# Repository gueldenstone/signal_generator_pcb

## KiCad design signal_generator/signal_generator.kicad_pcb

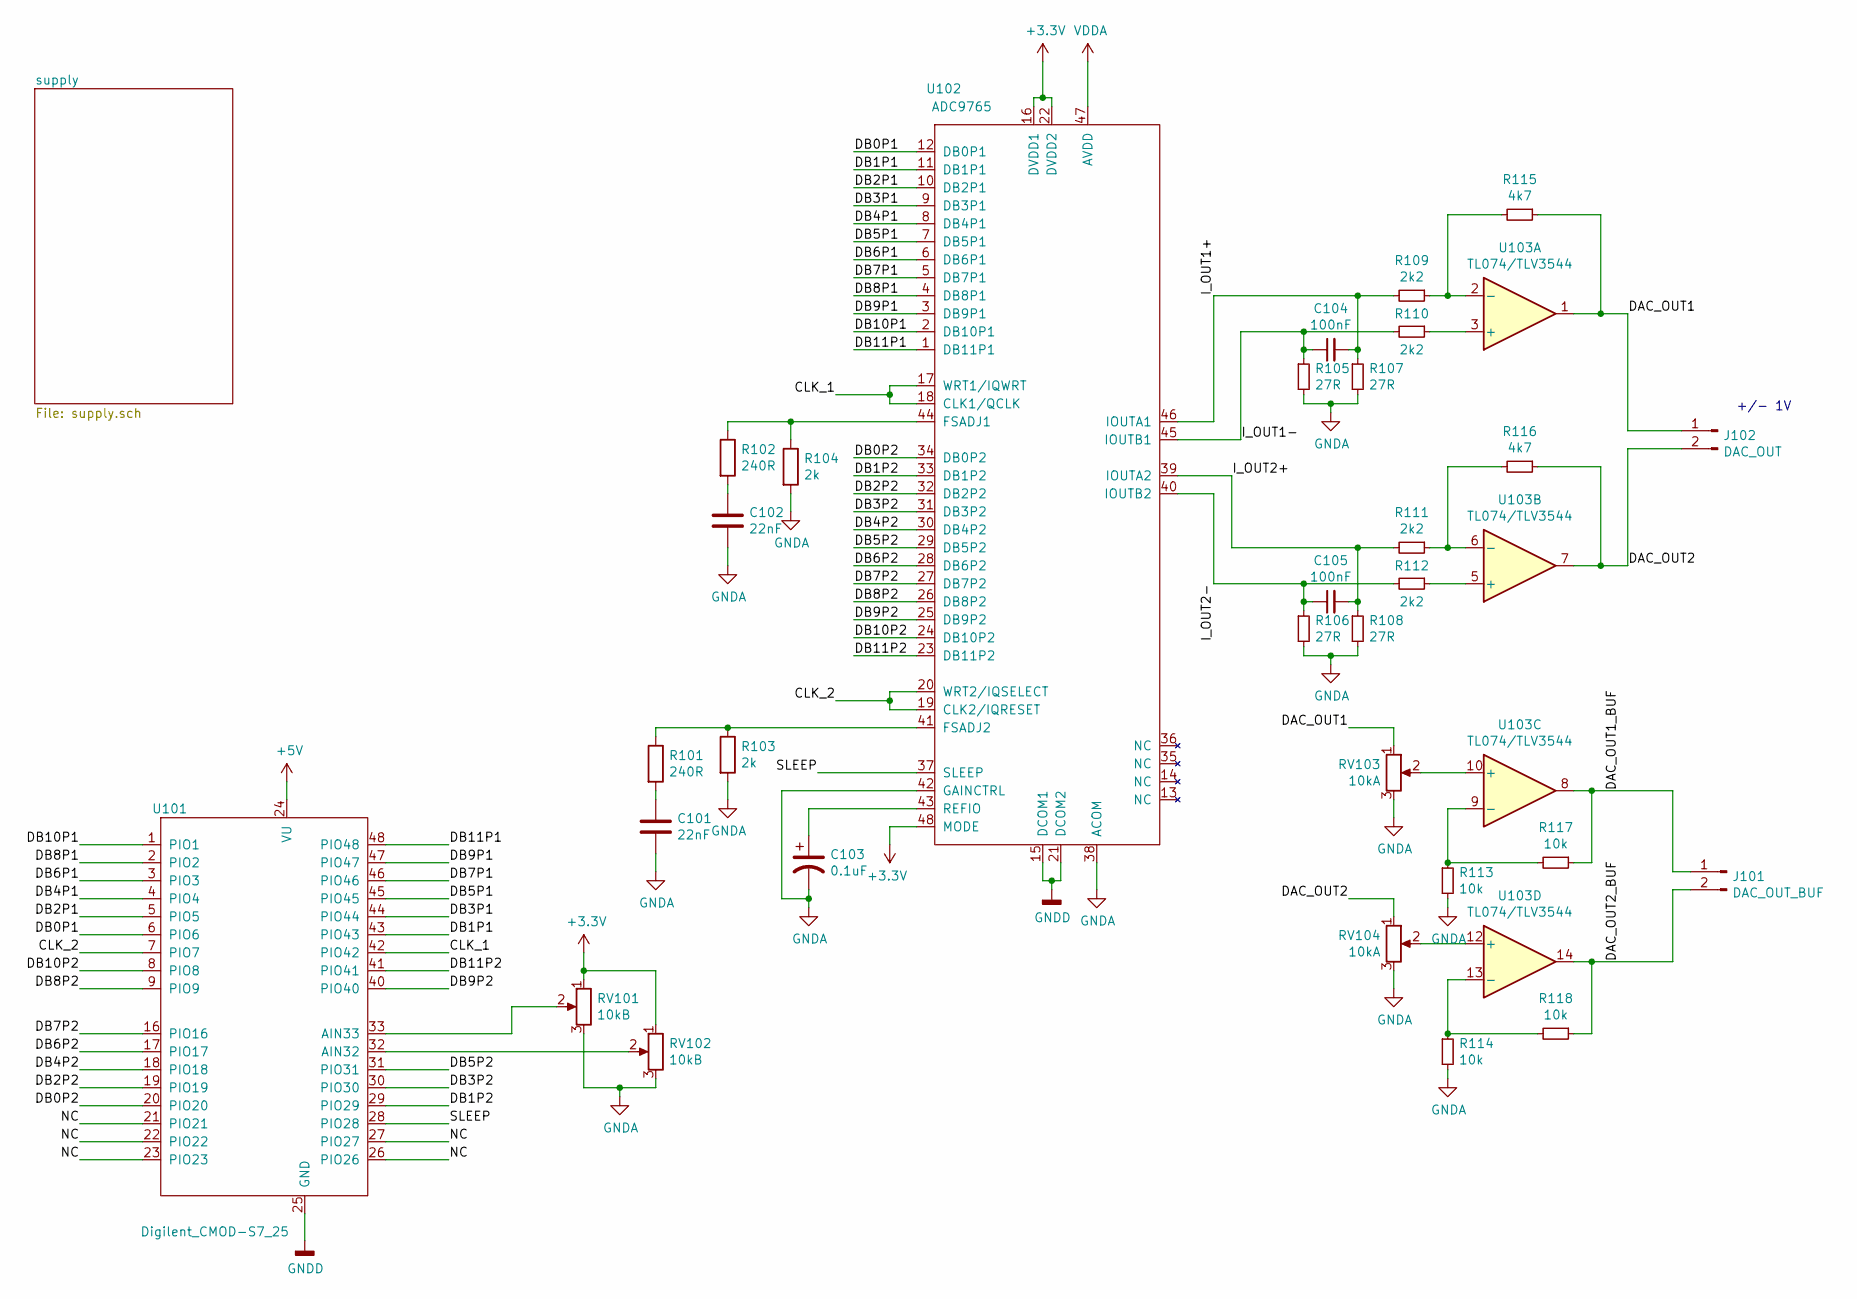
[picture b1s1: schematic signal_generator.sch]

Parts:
C101, C102: 22nF; C_0603_1608Metric_Pad1.08x0.95mm_HandSolder
C103: 0.1uF; C_0603_1608Metric_Pad1.08x0.95mm_HandSolder
C104, C105: 100nF; C_0603_1608Metric_Pad1.08x0.95mm_HandSolder
J101: DAC_OUT_BUF; PinHeader_1x02_P2.54mm_Vertical
J102: DAC_OUT; PinHeader_1x02_P2.54mm_Vertical
R101, R102: 240R; R_0603_1608Metric_Pad0.98x0.95mm_HandSolder
R103, R104: 2k; R_0603_1608Metric_Pad0.98x0.95mm_HandSolder
R105, R106, R107, R108: 27R; R_0603_1608Metric_Pad0.98x0.95mm_HandSolder
R109, R110, R111, R112: 2k2; R_0603_1608Metric_Pad0.98x0.95mm_HandSolder
R113, R114, R117, R118: 10k; R_0603_1608Metric_Pad0.98x0.95mm_HandSolder
R115, R116: 4k7; R_0603_1608Metric_Pad0.98x0.95mm_HandSolder
RV101, RV102: 10kB; Potentiometer_Alpha_RD901F-40-00D_Single_Vertical_CircularH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
RV103, RV104: 10kA; Potentiometer_Alpha_RD901F-40-00D_Single_Vertical_CircularH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
U101: Digilent_CMOD-S7_25; CMODS7-25
U102: ADC9765; LQFP-48_7x7mm_P0.5mm
U103: TL074/TLV3544; SOIC-14_3.9x8.7mm_P1.27mm

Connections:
+3V3: RV101.1, RV102.1, U102.16 (DVDD1), U102.22 (DVDD2), U102.48 (MODE); also elsewhere on the board
/CLK_1: U101.42 (PIO42), U102.17 (WRT1/IQWRT), U102.18 (CLK1/QCLK)
/CLK_2: U101.7 (PIO7), U102.19 (CLK2/IQRESET), U102.20 (WRT2/IQSELECT)
/DAC_OUT1: J102.1, R115.1, RV103.1, U103.1
/DAC_OUT1_BUF: J101.1, R117.1, U103.8
/DAC_OUT2: J102.2, R116.1, RV104.1, U103.7
/DAC_OUT2_BUF: J101.2, R118.1, U103.14
/DB0P1: U101.6 (PIO6), U102.12 (DB0P1)
/DB0P2: U101.20 (PIO20), U102.34 (DB0P2)
/DB1P1: U101.43 (PIO43), U102.11 (DB1P1)
/DB1P2: U101.29 (PIO29), U102.33 (DB1P2)
/DB2P1: U101.5 (PIO5), U102.10 (DB2P1)
/DB2P2: U101.19 (PIO19), U102.32 (DB2P2)
/DB3P1: U101.44 (PIO44), U102.9 (DB3P1)
/DB3P2: U101.30 (PIO30), U102.31 (DB3P2)
/DB4P1: U101.4 (PIO4), U102.8 (DB4P1)
/DB4P2: U101.18 (PIO18), U102.30 (DB4P2)
/DB5P1: U101.45 (PIO45), U102.7 (DB5P1)
/DB5P2: U101.31 (PIO31), U102.29 (DB5P2)
/DB6P1: U101.3 (PIO3), U102.6 (DB6P1)
/DB6P2: U101.17 (PIO17), U102.28 (DB6P2)
/DB7P1: U101.46 (PIO46), U102.5 (DB7P1)
/DB7P2: U101.16 (PIO16), U102.27 (DB7P2)
/DB8P1: U101.2 (PIO2), U102.4 (DB8P1)
/DB8P2: U101.9 (PIO9), U102.26 (DB8P2)
/DB9P1: U101.47 (PIO47), U102.3 (DB9P1)
/DB9P2: U101.40 (PIO40), U102.25 (DB9P2)
/DB10P1: U101.1 (PIO1), U102.2 (DB10P1)
/DB10P2: U101.8 (PIO8), U102.24 (DB10P2)
/DB11P1: U101.48 (PIO48), U102.1 (DB11P1)
/DB11P2: U101.41 (PIO41), U102.23 (DB11P2)
/I_OUT1+: C104.2, R107.1, R109.2, U102.46 (IOUTA1)
/I_OUT1-: C104.1, R105.1, R110.2, U102.45 (IOUTB1)
/I_OUT2+: C105.2, R108.1, R111.2, U102.39 (IOUTA2)
/I_OUT2-: C105.1, R106.1, R112.2, U102.40 (IOUTB2)
/NC: U101.21 (PIO21), U101.22 (PIO22), U101.23 (PIO23), U101.26 (PIO26), U101.27 (PIO27)
/SLEEP: U101.28 (PIO28), U102.37 (SLEEP)
GND: U101.25 (GND), U102.15 (DCOM1), U102.21 (DCOM2); also elsewhere on the board
GNDA: C101.2, C102.2, C103.2, R103.2, R104.2, R105.2, R106.2, R107.2, R108.2, R113.2, R114.2, RV101.3, RV102.3, RV103.3, RV104.3, U102.38 (ACOM), U102.42 (GAINCTRL); also elsewhere on the board
unnamed: C101.1, R101.2
unnamed: C102.1, R102.2
unnamed: C103.1, U102.43 (REFIO)
unnamed: R101.1, R103.1, U102.41 (FSADJ2)
unnamed: R102.1, R104.1, U102.44 (FSADJ1)
unnamed: R109.1, R115.2, U103.2 (-)
unnamed: R110.1, U103.3 (+)
unnamed: R111.1, R116.2, U103.6 (-)
unnamed: R112.1, U103.5 (+)
unnamed: R113.1, R117.2, U103.9 (-)
unnamed: R114.1, R118.2, U103.13 (-)
unnamed: RV101.2, U101.33 (AIN33)
unnamed: RV102.2, U101.32 (AIN32)
unnamed: RV103.2, U103.10 (+)
unnamed: RV104.2, U103.12 (+)
VDDA: U102.47 (AVDD), U103.4 (V+); also elsewhere on the board
VSSA: U103.11 (V-); also elsewhere on the board

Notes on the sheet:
+/- 1V

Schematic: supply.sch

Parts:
C201, C206, C212, C213: 10u; 153CLV-0405
C202, C211: 22u; C0805
C203, C204, C205, C207, C208: 100nF; C_0603_1608Metric
C209: 2u2; C0805
C210: 1n; C0805
D201: MBR0520LT; SOD123
J201: Power Input; PinSocket_1x02_P2.54mm_Vertical
J202: Power Output; PinHeader_1x05_P2.54mm_Vertical
L201, L202: 22u; L0315
L203: 5uH; L_0805_2012Metric
R201: 29k4; C0805
R202: 10k; C0805
R203, R204, R205, R206: 30k; C0805
U103: TL074; SSOP-14_5.3x6.2mm_P0.65mm
U201: TPS76933; SOT23-DBV
U202: LM2611; SOT23-DBV
U203: TPS76901; SOT23-DBV
U204: TPS72301; SOT23-DBV

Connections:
+3V3: C205.1, C206.1, C207.1, J202.1, U201.5; also elsewhere on the board
-5V: C211.2, L202.1, U204.2 (IN), U204.3 (EN)
GND: C201.2, C202.1, C205.2, C206.2, C207.2, C211.1, D201.1, J201.1, J202.2, L203.2, R202.2, U201.2, U201.3, U202.2 (GND); also elsewhere on the board
GNDA: C203.2, C204.1, C208.2, C212.2, C213.1, J202.4, L203.1, R204.2, R206.2, U203.2, U203.3, U204.1 (GND); also elsewhere on the board
unnamed: C209.1, D201.2, L202.2
unnamed: C209.2, C210.1, L201.1, R201.1, U202.1 (SW)
unnamed: C210.2, R201.2, R202.1, U202.3 (NFB)
unnamed: R203.2, R204.1, U203.4
unnamed: R205.2, R206.1, U204.4 (NR)
VDDA: C203.1, C208.1, C212.1, J202.3, R203.1, U103.4 (V+), U203.5; also elsewhere on the board
VSSA: C204.2, C213.2, J202.5, R205.1, U103.11 (V-), U204.5 (OUT)

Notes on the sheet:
+4V fixed, Analog
-4V fixed, Analog

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
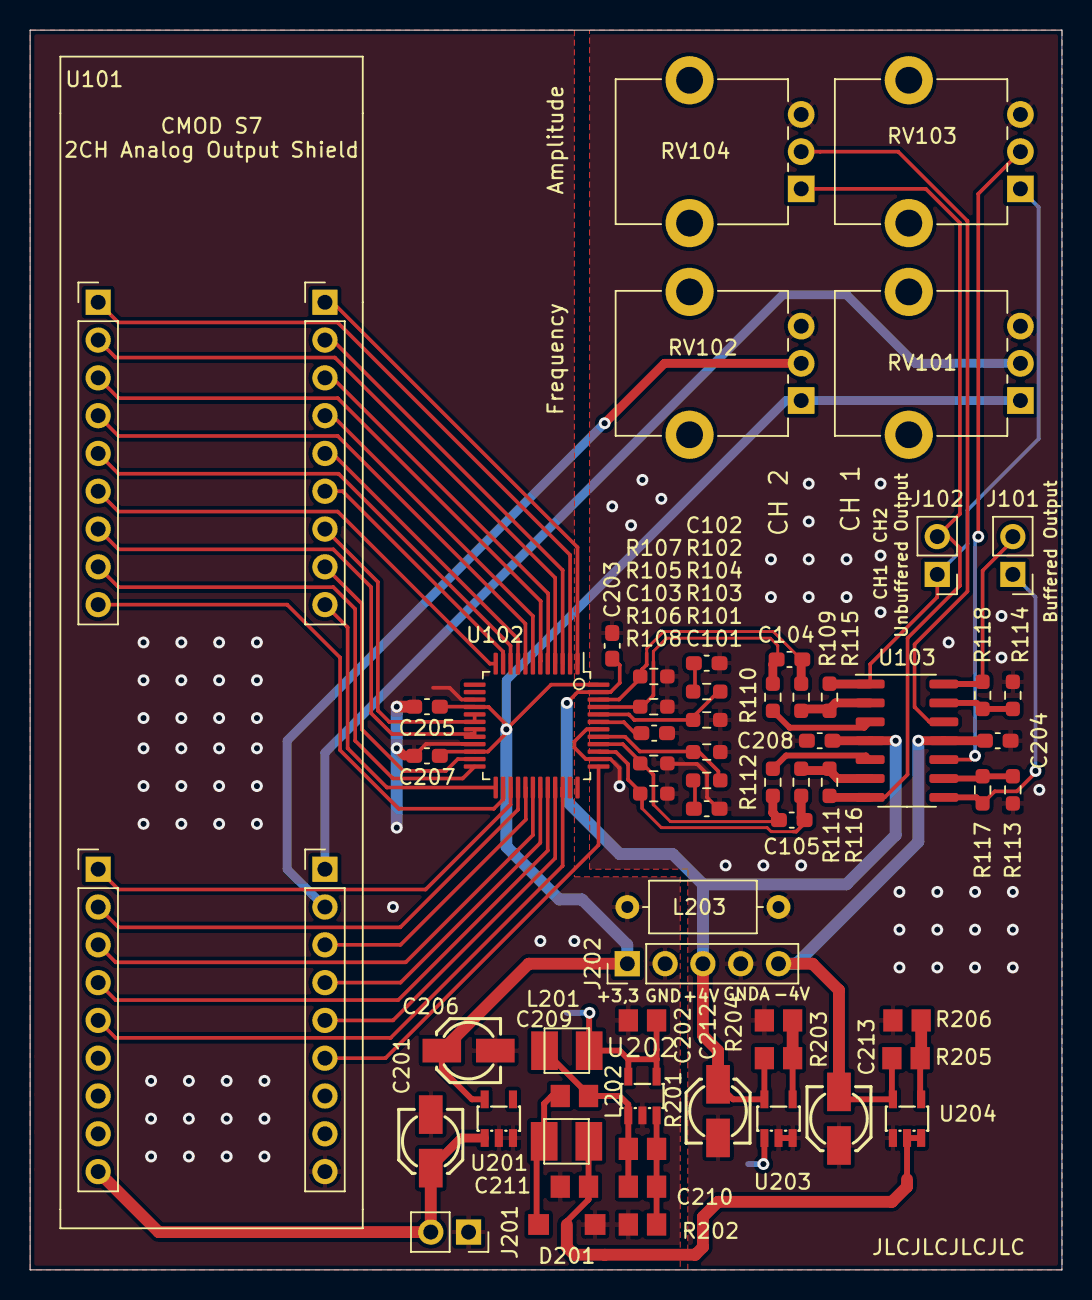
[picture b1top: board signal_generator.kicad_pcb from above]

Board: 2 copper layers, 69.3 x 83.3 mm, 61 parts (0 on the bottom side), 63 nets.

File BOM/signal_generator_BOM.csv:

"Id";"Designator";"Package";"Quantity";"Designation";"Supplier and ref";
1;"L203";"L_Axial_L7.0mm_D3.3mm_P10.16mm_Horizontal_Fastron_MICC";1;"5uH";;;
2;"R118,R117,R114,R113";"R_0603_1608Metric_Pad0.98x0.95mm_HandSolder";4;"10k";;;
3;"R116,R115";"R_0603_1608Metric_Pad0.98x0.95mm_HandSolder";2;"4k7";;;
4;"R112,R111,R110,R109";"R_0603_1608Metric_Pad0.98x0.95mm_HandSolder";4;"2k2";;;
5;"R108,R107,R106,R105";"R_0603_1608Metric_Pad0.98x0.95mm_HandSolder";4;"22R";;;
6;"R104,R103";"R_0603_1608Metric_Pad0.98x0.95mm_HandSolder";2;"2k";;;
7;"R102,R101";"R_0603_1608Metric_Pad0.98x0.95mm_HandSolder";2;"240R";;;
8;"C208,C207,C205,C204,C203,C105,C104";"C_0603_1608Metric_Pad1.08x0.95mm_HandSolder";7;"100nF";;;
9;"C103";"C_0603_1608Metric_Pad1.08x0.95mm_HandSolder";1;"0.1uF";;;
10;"C102,C101";"C_0603_1608Metric_Pad1.08x0.95mm_HandSolder";2;"22nF";;;
11;"L202,L201";"L0315";2;"22u";;;
12;"U103";"SOIC-14_3.9x8.7mm_P1.27mm";1;"TL074/TLV3544";;;
13;"U204";"SOT23-DBV";1;"TPS72301";;;
14;"U203";"SOT23-DBV";1;"TPS76901";;;
15;"U202";"SOT23-DBV";1;"LM2611";;;
16;"U201";"SOT23-DBV";1;"TPS76933";;;
17;"R206,R205,R204,R203";"C0805";4;"30k";;;
18;"R202";"C0805";1;"10k";;;
19;"R201";"C0805";1;"29k4";;;
20;"J202";"PinHeader_1x05_P2.54mm_Vertical";1;"Power Output";;;
21;"J201";"PinSocket_1x02_P2.54mm_Vertical";1;"Power Input";;;
22;"D201";"SOD123";1;"MBR0520LT";;;
23;"C213,C212,C206,C201";"153CLV-0405";4;"10u";;;
24;"C211,C202";"C0805";2;"22u";;;
25;"C210";"C0805";1;"1n";;;
26;"C209";"C0805";1;"2u2";;;
27;"U101";"CMODS7-25";1;"Digilent_CMOD-S7_25";;;
28;"RV104,RV103";"Potentiometer_Alpha_RD901F-40-00D_Single_Vertical_CircularHoles";2;"10kA";;;
29;"RV102,RV101";"Potentiometer_Alpha_RD901F-40-00D_Single_Vertical_CircularHoles";2;"10kB";;;
30;"J101";"PinHeader_1x02_P2.54mm_Vertical";1;"DAC_OUT_BUF";;;
31;"U102";"LQFP-48_7x7mm_P0.5mm";1;"ADC9765";;;
32;"J102";"PinHeader_1x02_P2.54mm_Vertical";1;"DAC_OUT";;;

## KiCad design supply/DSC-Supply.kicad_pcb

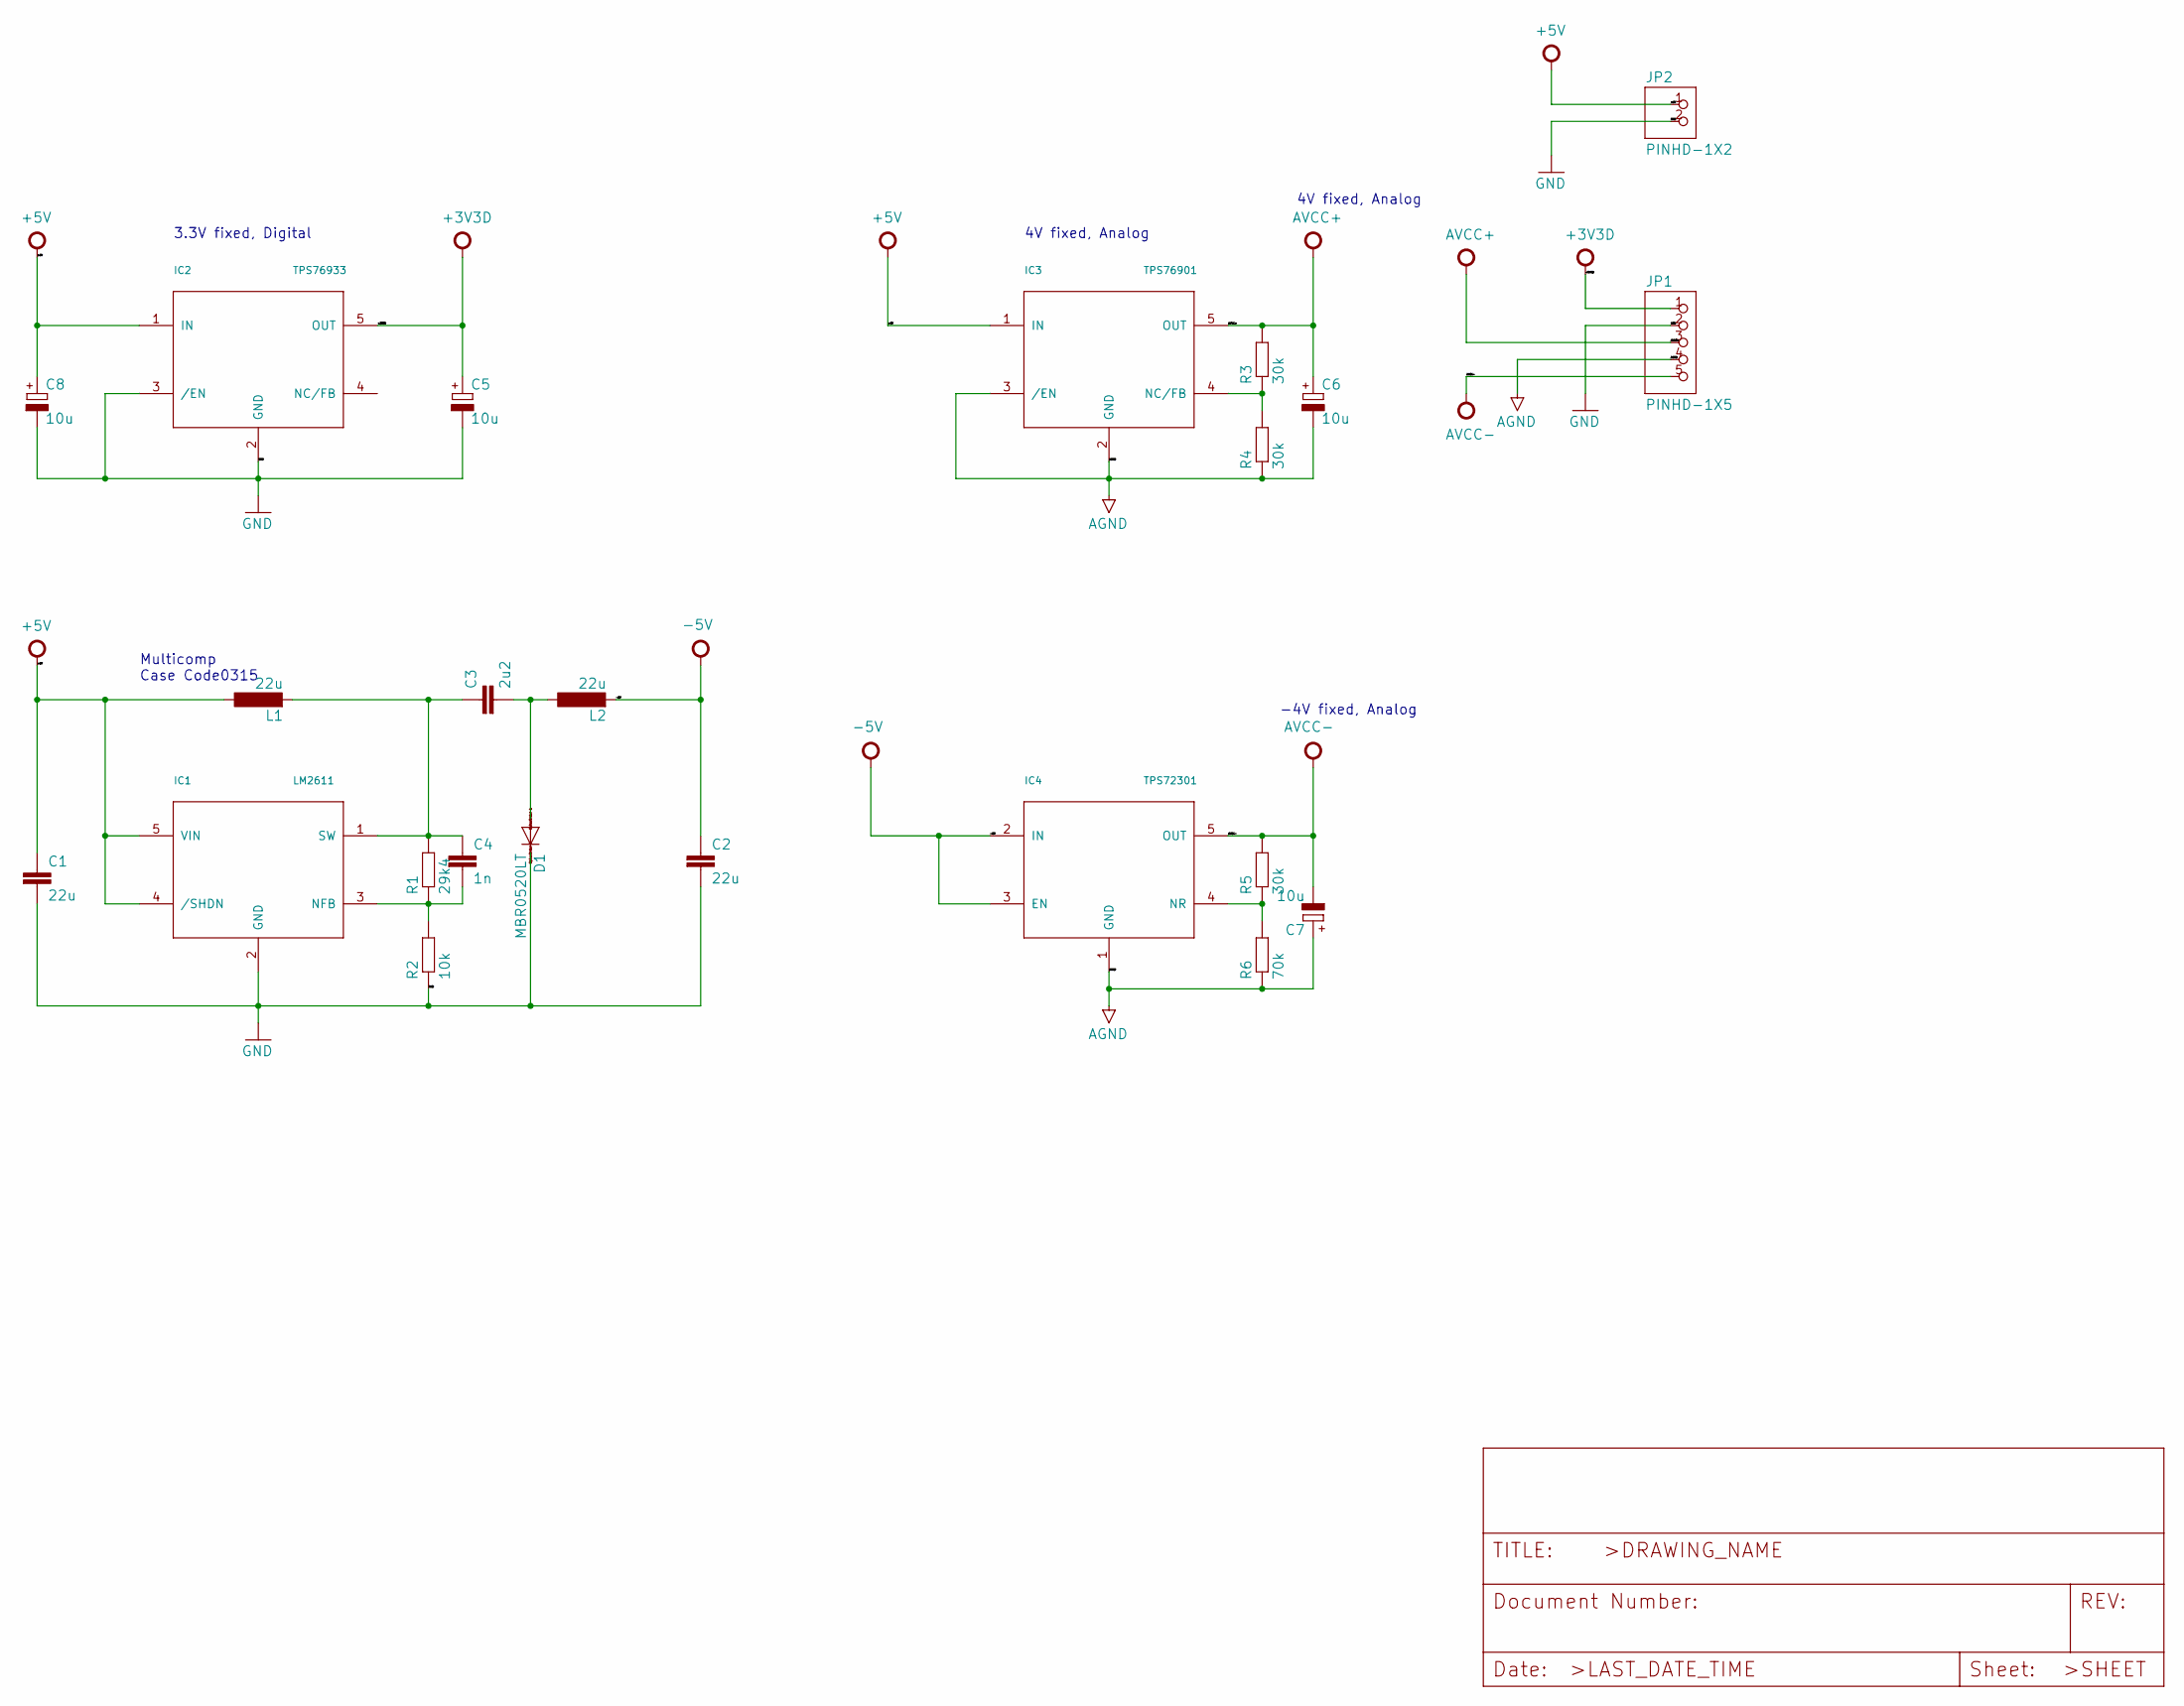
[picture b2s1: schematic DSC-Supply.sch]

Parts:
C1, C2: 22u; C0805
C3: 2u2; C0805
C4: 1n; C0805
C5, C6, C7, C8: 10u; 153CLV-0405
D1: MBR0520LT; SOD123
IC1: LM2611; SOT23-DBV
IC2: TPS76933; SOT23-DBV
IC3: TPS76901; SOT23-DBV
IC4: TPS72301; SOT23-DBV
JP1: PINHD-1X5; 1X05
JP2: PINHD-1X2; 1X02
L1, L2: 22u; L0315
R1: 29k4; R0805
R2: 10k; R0805
R3, R4, R5: 30k; R0805
R6: 70k; R0805

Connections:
+3V3D: C5.+, IC2.5 (OUT), JP1.1
+5V: C1.1, C8.+, IC1.4 (/SHDN), IC1.5 (VIN), IC2.1 (IN), IC3.1 (IN), JP2.1, L1.1
-5V: C2.1, IC4.2 (IN), IC4.3 (EN), L2.2
AGND: C6.-, C7.+, IC3.2 (GND), IC3.3 (/EN), IC4.1 (GND), JP1.4, R4.1, R6.1
AVCC+: C6.+, IC3.5 (OUT), JP1.3, R3.2
AVCC-: C7.-, IC4.5 (OUT), JP1.5, R5.2
GND: C1.2, C2.2, C5.-, C8.-, D1.C, IC1.2 (GND), IC2.2 (GND), IC2.3 (/EN), JP1.2, JP2.2, R2.1
unnamed: C3.1, C4.1, IC1.1 (SW), L1.2, R1.2
unnamed: C3.2, D1.A, L2.1
unnamed: C4.2, IC1.3 (NFB), R1.1, R2.2
unnamed: IC3.4 (NC/FB), R3.1, R4.2
unnamed: IC4.4 (NR), R5.1, R6.2

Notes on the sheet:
Multicomp Case Code0315
3.3V fixed, Digital
4V fixed, Analog
-4V fixed, Analog

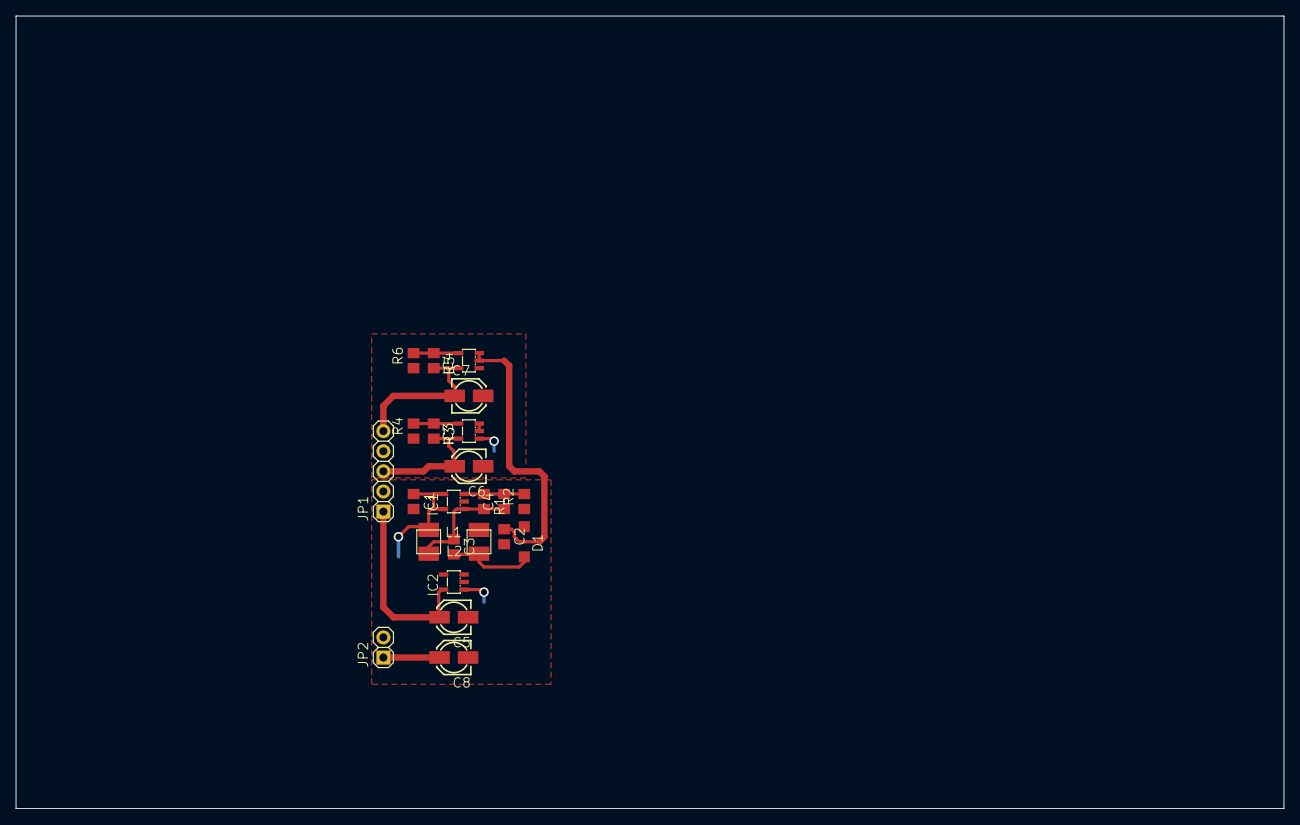
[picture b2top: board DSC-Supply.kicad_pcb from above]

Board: 2 copper layers, 160.0 x 100.0 mm, 23 parts (0 on the bottom side), 12 nets.

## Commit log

2020-10-19 Version 1 with all libs
2020-10-29 new pcb design and pin layout
2020-11-02 added power supply, integrated in schematic
2020-11-07 finished PCB v1
2020-11-07 cleanup
2020-11-08 added author to pcb
2020-11-10 send to production
2020-12-09 final status
